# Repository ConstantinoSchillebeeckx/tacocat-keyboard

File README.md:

# tacocat keyboard

:construction: this repo is currently on *hold*; once I started writing the firmware, I realized the choice of microcontroller was not a good one. For a keyboard, it's super useful to have a USB to serial chip that acts like a [HID](https://en.wikipedia.org/wiki/Human_interface_device), that's why the Teensy or the ATmega32U4 are popular options. That being said, I started developing the firmware in such a way that required a python script to be running on the host to listen to the keystrokes being sent. :sweat: Furthermore, I'm not convinced that the physical layout is that great. Anywho, I'm leaving this here for reference. :construction:

<br>
<br>

Another split ergonomic keyboard with features:
- two symmetric keyboard halves staggered in opposite directions
- wireless or powered operation
- wifi & bluetooth connected
- can be used as two halves with a TRRS audio cable or as single joined keyboard (no cable needed)
- audio passthrough

Please visit the [wiki](https://github.com/ConstantinoSchillebeeckx/tacocat-keyboard/wiki) for full documentation and build logs.

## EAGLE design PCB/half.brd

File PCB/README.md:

# PCB

The PCB was designed to be symmetric so that the same half could be used for both the left and the right side of the keyboard; the PCB simply needs to be flipped over depending on the side that is used.

Features:
- two symmetric keyboard halves
- wireless or powered operation
- wifi & bluetooth connected
- can be used as two halves with a TRRS audio cable or as single joined keyboard (no cable needed)
- audio passthrough

The board can be ordered from OshPark by clicking the image below.

<a href="https://oshpark.com/shared_projects/jsQ9hCTr"></img></a>

## Notes

To populate, place all Cherry MX switches, LEDs, diodes, capacitors and resistors on the *top* side of the board; the ESP32 and all IO jacks are placed on the *bottom* of the PCB.

Also:
- the top TRRS jack may hit one of the alignment pins of the switch; this pins may have to be manually cut
- the male I2C connection has plastic alignment pins that will only fit into the PCB after the two existing holes (used by the female end) are drilled out to a diamter of 1mm

## BOM

The items listed below are for two keyboard halves; an [online BOM](https://www.digikey.com/classic/RegisteredUser/BOMBillOfMaterials.aspx?path=1&exist=1&id=5155922) has also been generated for ease of purchase.

**NOTE:** the BOM listed includes various USB & TRRS jacks needed to build custom cables for the project, however the list does not include the wires needed to build the cables. You'll need to source a 5 conductor cable to connect the keyboard halves and an 8 conductor cable (4 for USB, 4 for TRRS) for the cable connecting the keyboard to the computer.

## Layout

#### Circuit schematic

#### PCB top

#### PCB bottom

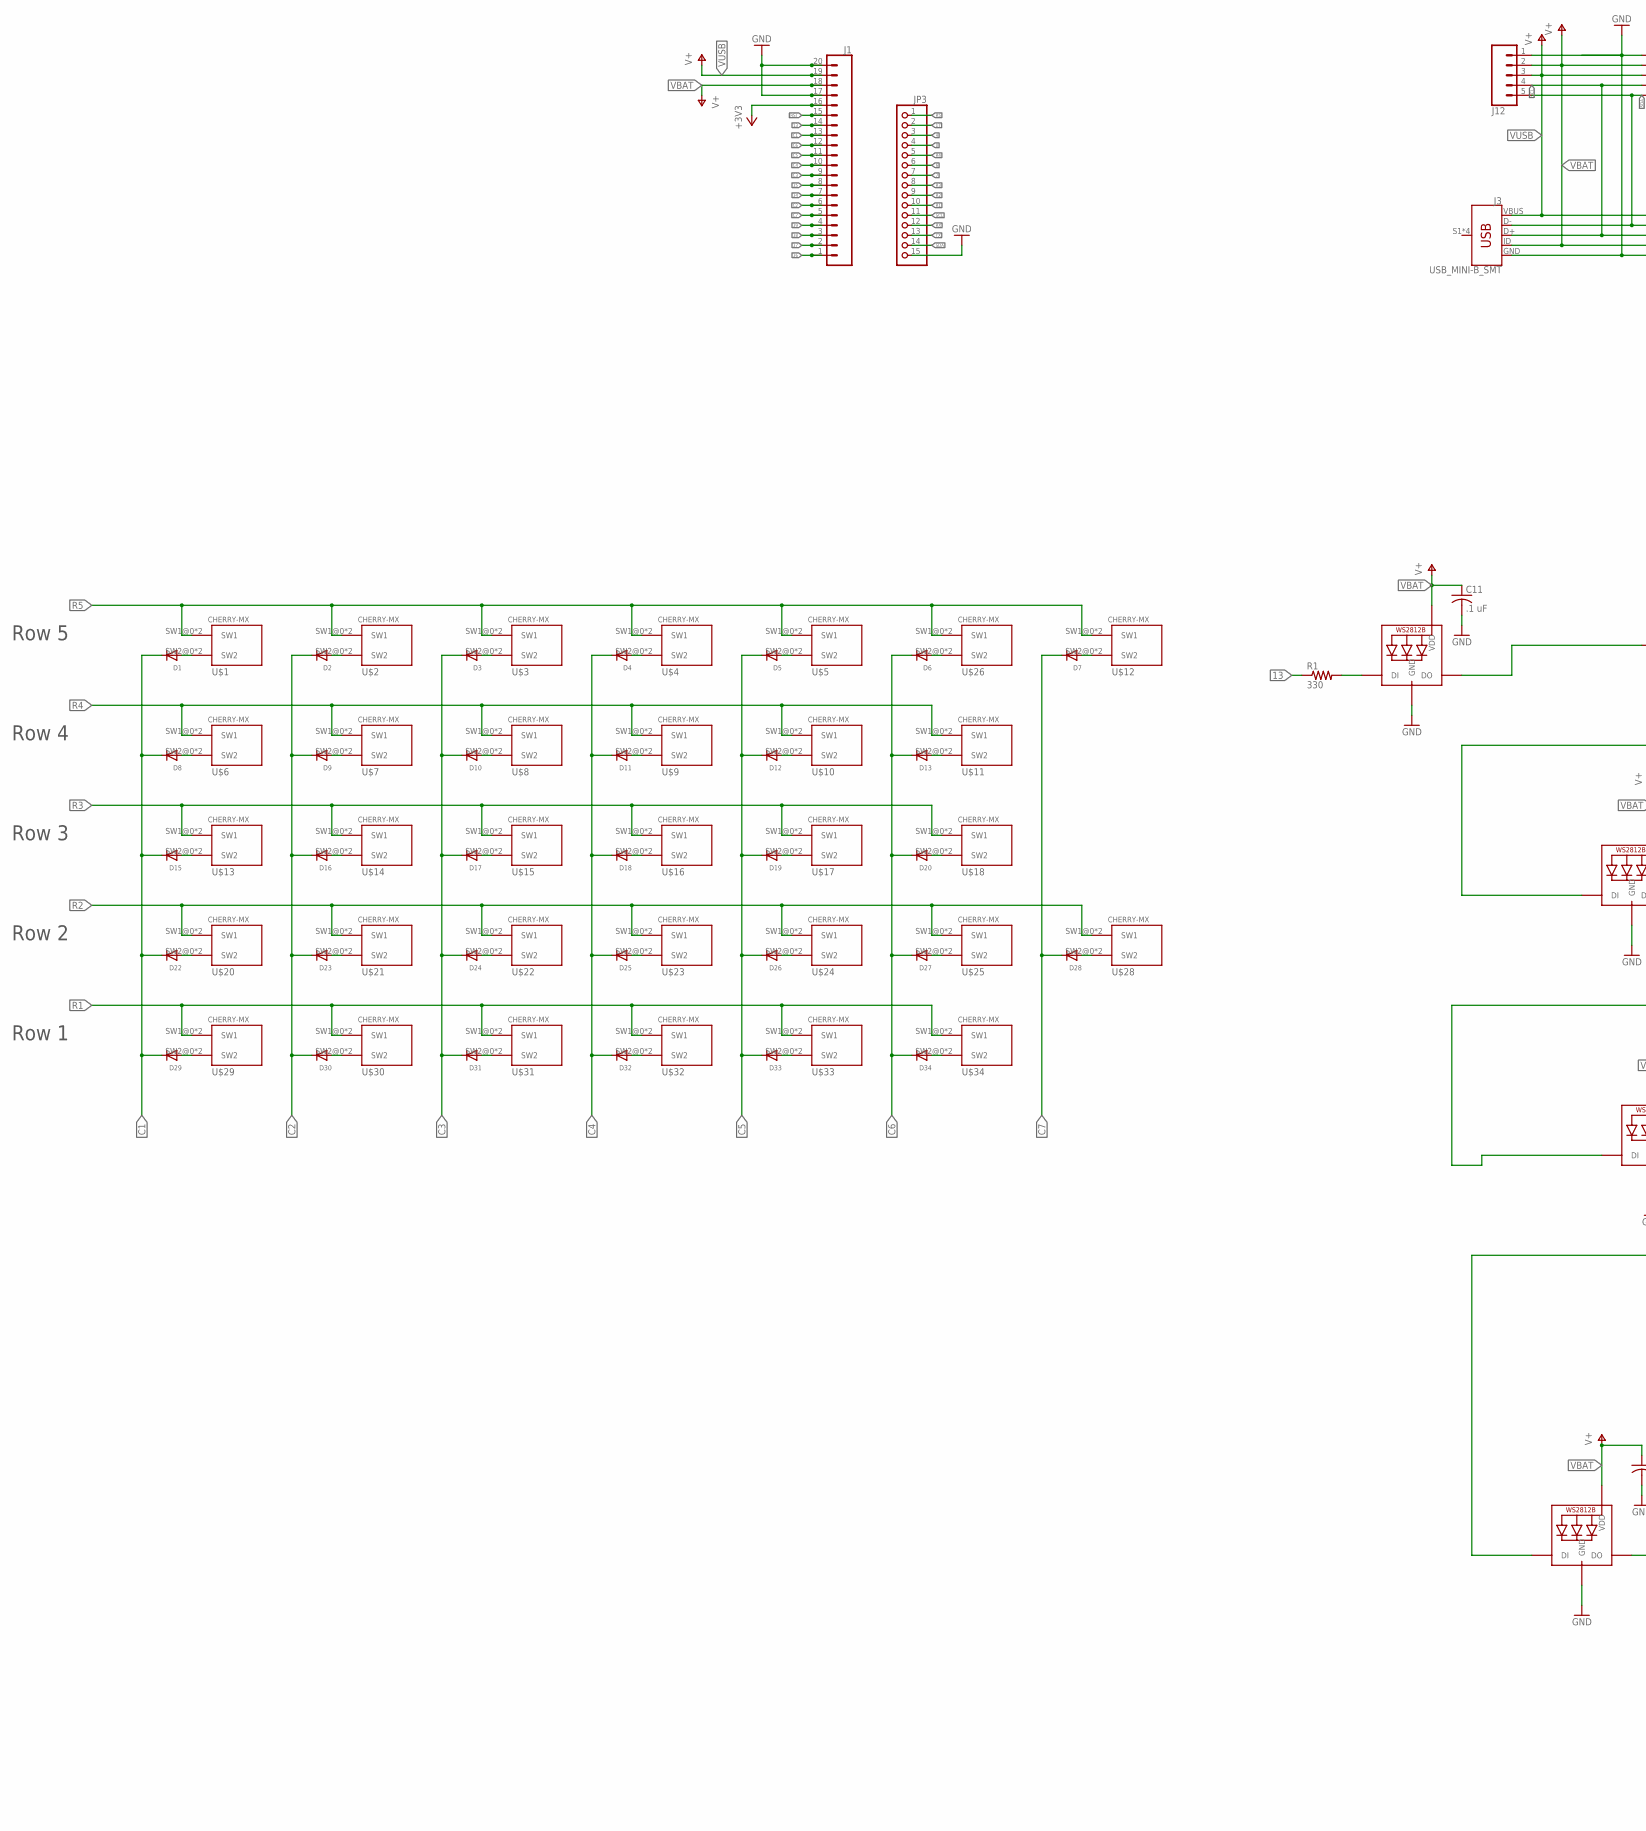
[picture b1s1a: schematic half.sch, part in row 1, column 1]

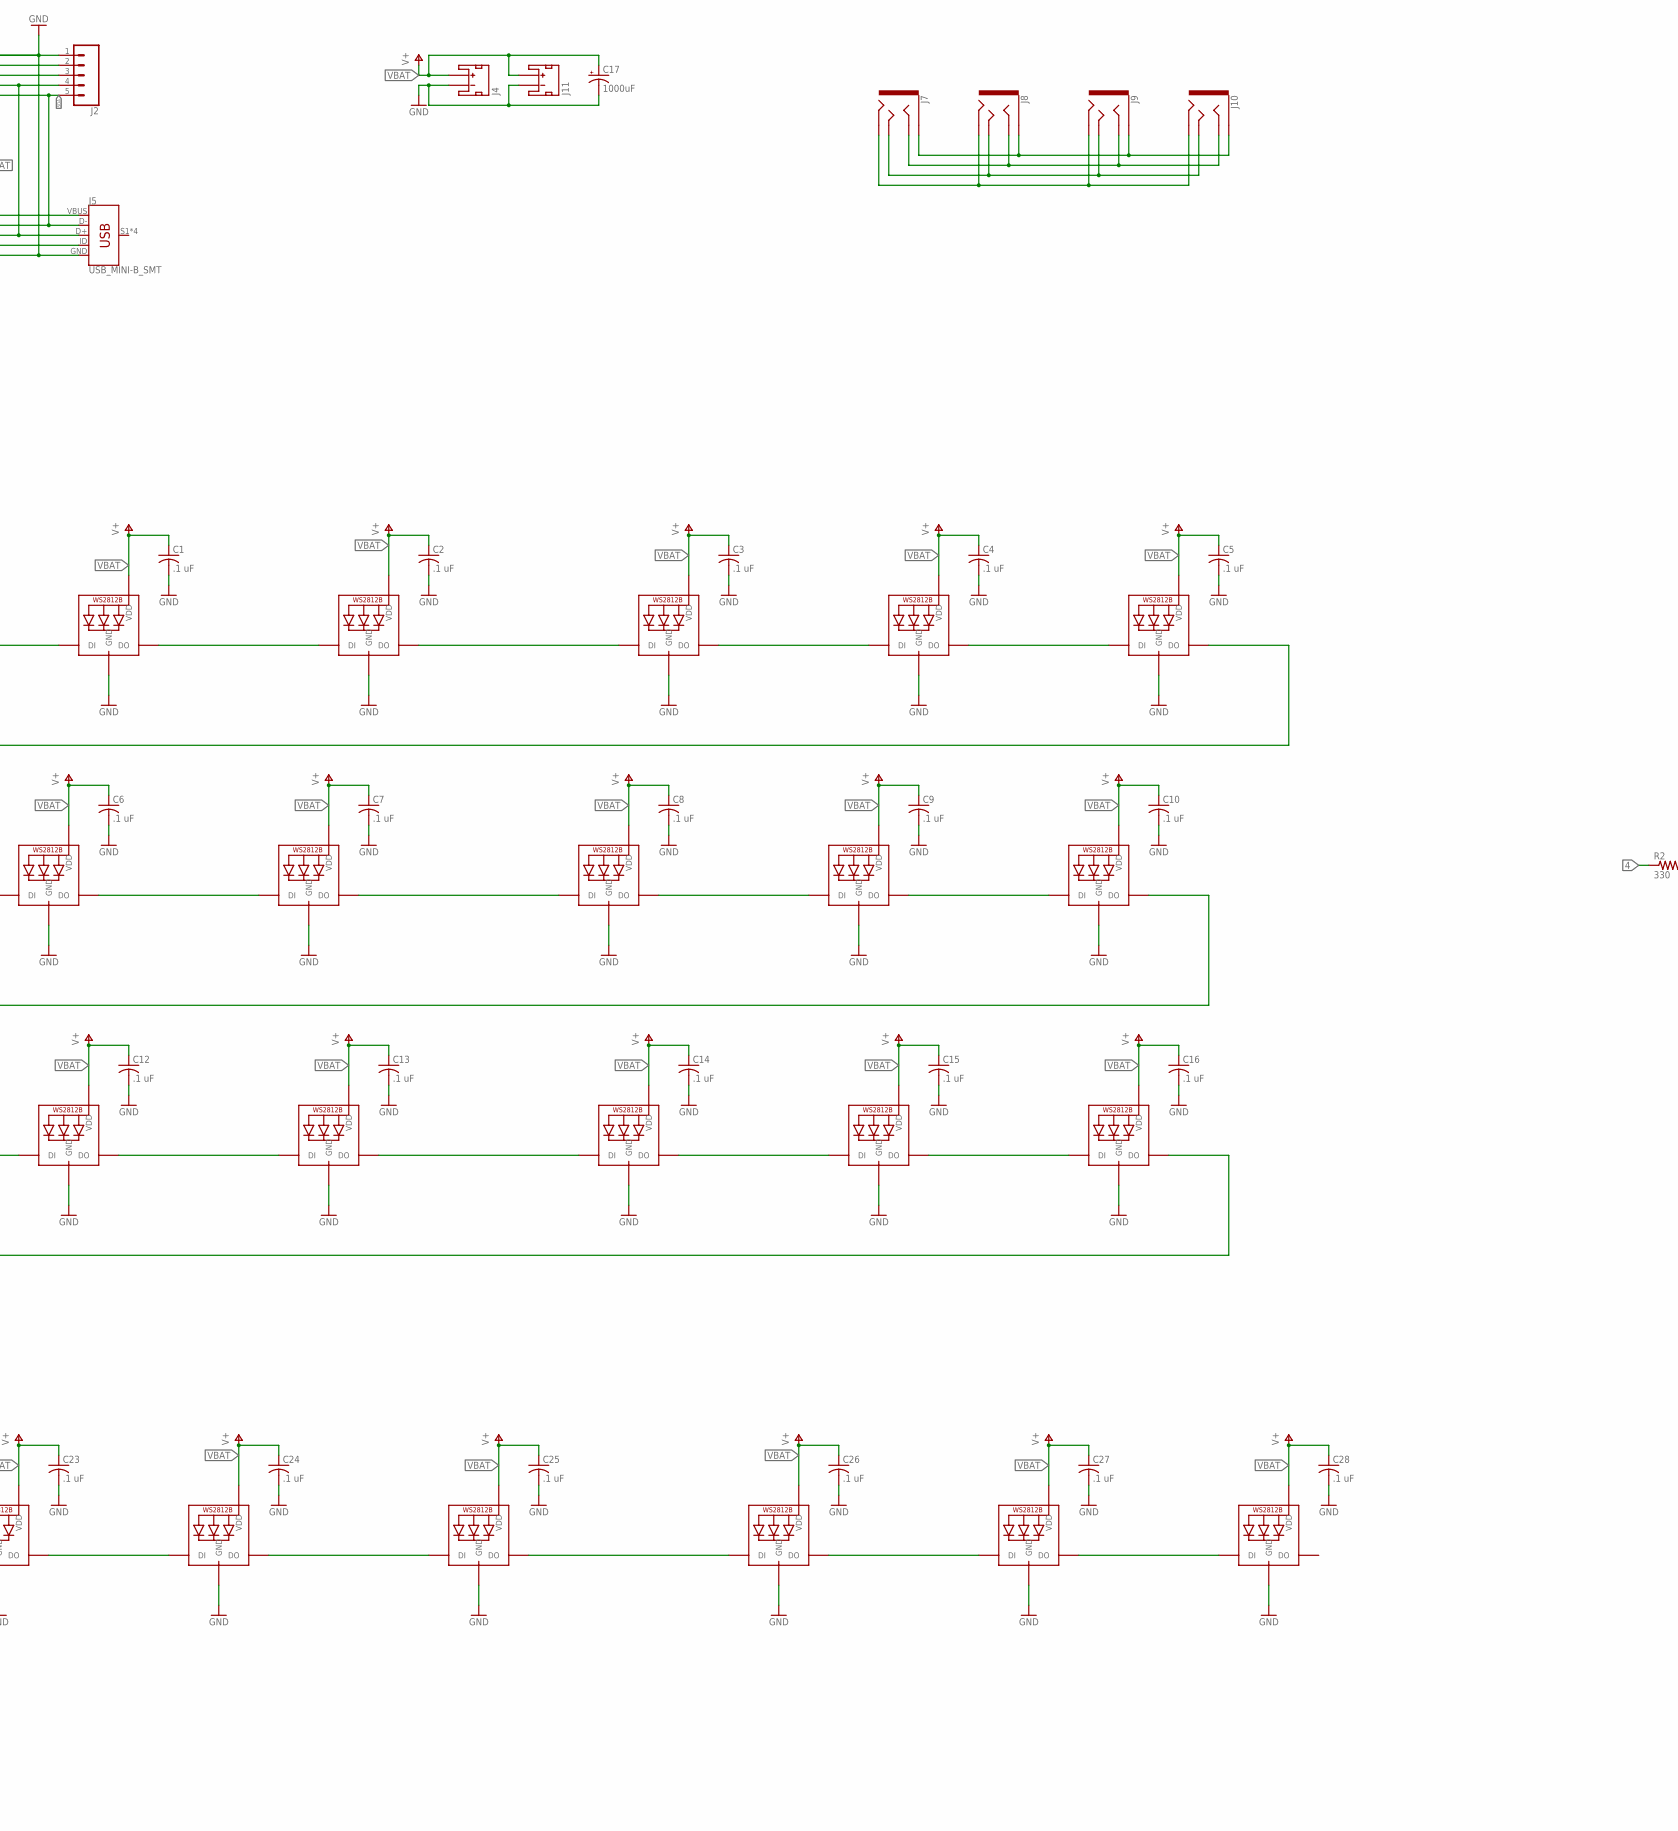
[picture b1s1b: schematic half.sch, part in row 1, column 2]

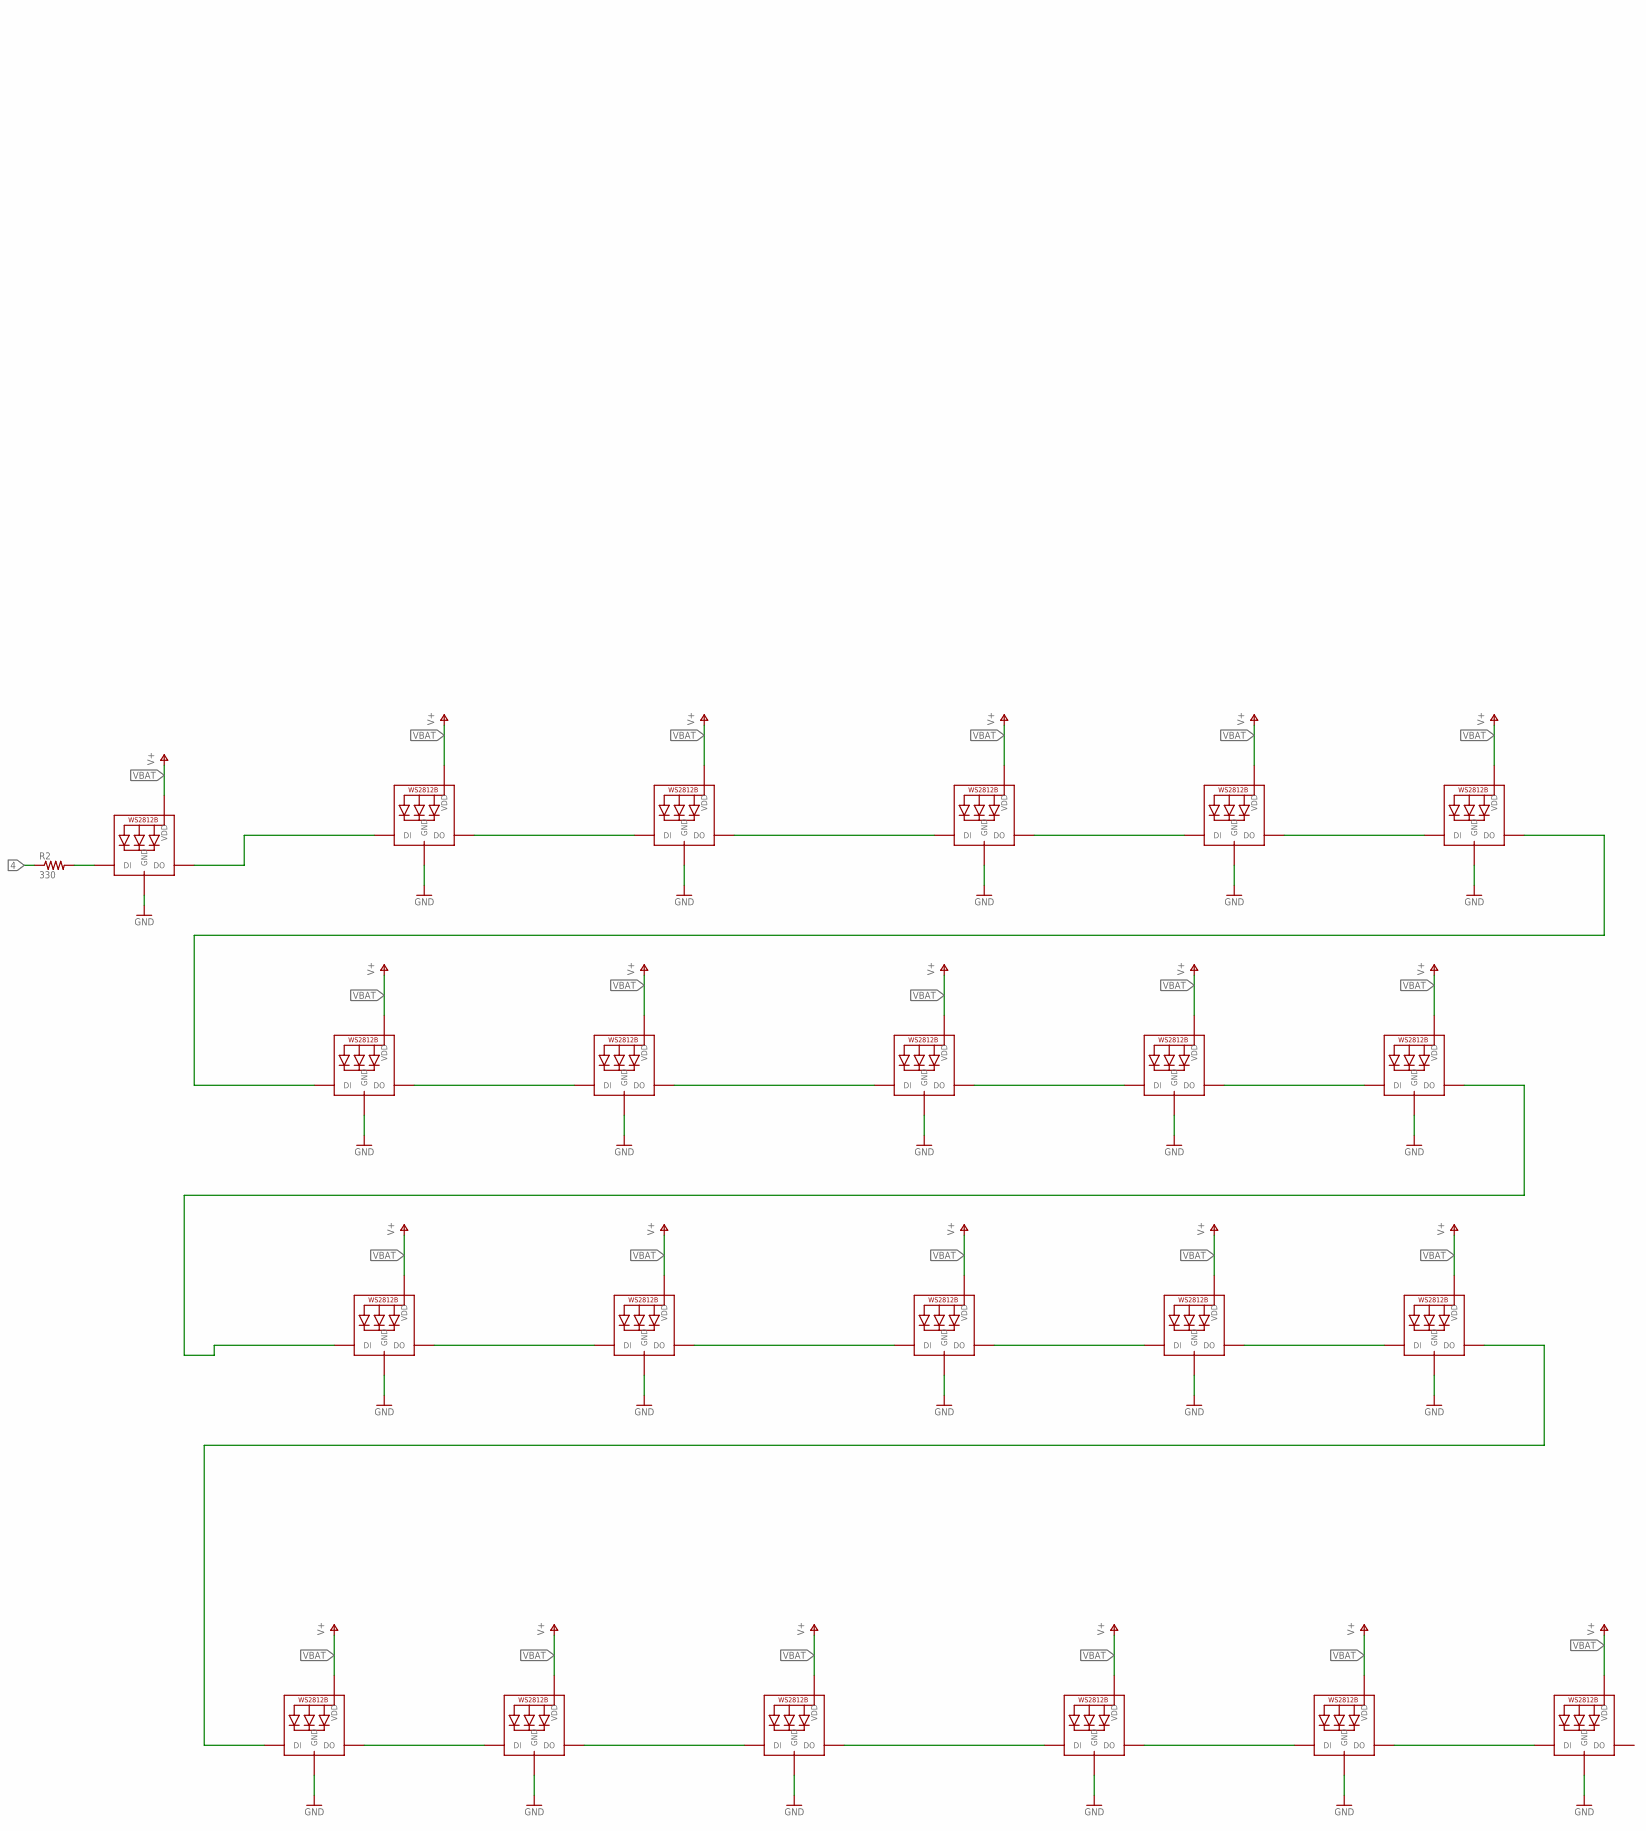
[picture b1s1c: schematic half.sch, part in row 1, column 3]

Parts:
C1, C2, C3, C4, C5, C6, C7, C8, C9, C10, C11, C12, C13, C14, C15, C16, C23, C24, C25, C26, C27, C28: .1 uF; C025-025X050
C17: 1000uF; E3,5-8
D1, D2, D3, D4, D5, D6, D7, D8, D9, D10, D11, D12, D13, D15, D16, D17, D18, D19, D20, D22, D23, D24, D25, D26, D27, D28, D29, D30, D31, D32, D33, D34: DIODEDO-1N4148; DO-1N4148
J1: CONN_20NOSILK; 1X20_NOSILK
J2: CONN_05NO_SILK_SMALL; 1X05_NO_SILK_SMALL
J3, J5: USB_MINI-B_SMT; USB-MINIB
J4, J11: JST_2MM_MALE; JST-2-SMD
J7, J8, J9, J10: AUDIO_JACK_TRRSSMD_RA; AUDIO_JACK_3.5MM_TRRS_SMD_RA
J12: CONN_05NO_SILK; 1X05_NO_SILK
JP3: PINHD-1X15-CB; 1X15-CB
LED1, LED2, LED3, LED4, LED5, LED6, LED7, LED8, LED9, LED10, LED11, LED12, LED13, LED14, LED15, LED16, LED17, LED18, LED19, LED20, LED21, LED22, LED23, LED24, LED25, LED26, LED27, LED28, LED29, LED30, LED31, LED32, LED33, LED34, LED35, LED36, LED37, LED38, LED39, LED40, LED41, LED42, LED43, LED44: WS2812BLONGPADS; WS2812B-NARROW-PADS
R1, R2: 330; 0204/7
U$1, U$2, U$3, U$4, U$5, U$6, U$7, U$8, U$9, U$10, U$11, U$12, U$13, U$14, U$15, U$16, U$17, U$18, U$20, U$21, U$22, U$23, U$24, U$25, U$26, U$28, U$29, U$30, U$31, U$32, U$33, U$34: CHERRY-MXSYMM-NOSILK; CHERRY-MX-SYMM-NOSILK

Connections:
0: JP3.4
4: JP3.3, R2.1
6: JP3.6
7: JP3.7
13: J1.14, R1.1
17: JP3.2
34: J1.7
35: J1.8
36: J1.1
37: J1.2
38: J1.3
39: J1.4
+3V3: J1.16
C1: D1.C, D8.C, D15.C, D22.C, D29.C, J1.13
C2: D2.C, D9.C, D16.C, D23.C, D30.C, J1.6
C3: D3.C, D10.C, D17.C, D24.C, D31.C, J1.9
C4: D4.C, D11.C, D18.C, D25.C, D32.C, J1.10
C5: D5.C, D12.C, D19.C, D26.C, D33.C, J1.11
C6: D6.C, D13.C, D20.C, D27.C, D34.C, J1.12
C7: D7.C, D28.C, J1.5
GND: C1.2, C2.2, C3.2, C4.2, C5.2, C6.2, C7.2, C8.2, C9.2, C10.2, C11.2, C12.2, C13.2, C14.2, C15.2, C16.2, C17.-, C23.2, C24.2, C25.2, C26.2, C27.2, C28.2, J1.17, J1.20, J2.1, J3.GND, J4.1 (-), J5.GND, J11.1 (-), J12.1, JP3.15, LED1.3-GND (GND), LED2.3-GND (GND), LED3.3-GND (GND), LED4.3-GND (GND), LED5.3-GND (GND), LED6.3-GND (GND), LED7.3-GND (GND), LED8.3-GND (GND), LED9.3-GND (GND), LED10.3-GND (GND), LED11.3-GND (GND), LED12.3-GND (GND), LED13.3-GND (GND), LED14.3-GND (GND), LED15.3-GND (GND), LED16.3-GND (GND), LED17.3-GND (GND), LED18.3-GND (GND), LED19.3-GND (GND), LED20.3-GND (GND), LED21.3-GND (GND), LED22.3-GND (GND), LED23.3-GND (GND), LED24.3-GND (GND), LED25.3-GND (GND), LED26.3-GND (GND), LED27.3-GND (GND), LED28.3-GND (GND), LED29.3-GND (GND), LED30.3-GND (GND), LED31.3-GND (GND), LED32.3-GND (GND), LED33.3-GND (GND), LED34.3-GND (GND), LED35.3-GND (GND), LED36.3-GND (GND), LED37.3-GND (GND), LED38.3-GND (GND), LED39.3-GND (GND), LED40.3-GND (GND), LED41.3-GND (GND), LED42.3-GND (GND), LED43.3-GND (GND), LED44.3-GND (GND)
unnamed: D1.A, U$1.SW2@0 (SW2), U$1.SW2@1 (SW2)
unnamed: D28.A, U$28.SW2@0 (SW2), U$28.SW2@1 (SW2)
unnamed: D8.A, U$6.SW2@0 (SW2), U$6.SW2@1 (SW2)
unnamed: D15.A, U$13.SW2@0 (SW2), U$13.SW2@1 (SW2)
unnamed: D22.A, U$20.SW2@0 (SW2), U$20.SW2@1 (SW2)
unnamed: D29.A, U$29.SW2@0 (SW2), U$29.SW2@1 (SW2)
unnamed: D7.A, U$12.SW2@0 (SW2), U$12.SW2@1 (SW2)
unnamed: D2.A, U$2.SW2@0 (SW2), U$2.SW2@1 (SW2)
unnamed: D9.A, U$7.SW2@0 (SW2), U$7.SW2@1 (SW2)
unnamed: D16.A, U$14.SW2@0 (SW2), U$14.SW2@1 (SW2)
unnamed: D30.A, U$30.SW2@0 (SW2), U$30.SW2@1 (SW2)
unnamed: D31.A, U$31.SW2@0 (SW2), U$31.SW2@1 (SW2)
unnamed: D24.A, U$22.SW2@0 (SW2), U$22.SW2@1 (SW2)
unnamed: D17.A, U$15.SW2@0 (SW2), U$15.SW2@1 (SW2)
unnamed: D10.A, U$8.SW2@0 (SW2), U$8.SW2@1 (SW2)
unnamed: D3.A, U$3.SW2@0 (SW2), U$3.SW2@1 (SW2)
unnamed: D4.A, U$4.SW2@0 (SW2), U$4.SW2@1 (SW2)
unnamed: D11.A, U$9.SW2@0 (SW2), U$9.SW2@1 (SW2)
unnamed: D18.A, U$16.SW2@0 (SW2), U$16.SW2@1 (SW2)
unnamed: D25.A, U$23.SW2@0 (SW2), U$23.SW2@1 (SW2)
unnamed: D32.A, U$32.SW2@0 (SW2), U$32.SW2@1 (SW2)
unnamed: D33.A, U$33.SW2@0 (SW2), U$33.SW2@1 (SW2)
unnamed: D26.A, U$24.SW2@0 (SW2), U$24.SW2@1 (SW2)
unnamed: D19.A, U$17.SW2@0 (SW2), U$17.SW2@1 (SW2)
unnamed: D12.A, U$10.SW2@0 (SW2), U$10.SW2@1 (SW2)
unnamed: D5.A, U$5.SW2@0 (SW2), U$5.SW2@1 (SW2)
unnamed: D6.A, U$26.SW2@0 (SW2), U$26.SW2@1 (SW2)
unnamed: D13.A, U$11.SW2@0 (SW2), U$11.SW2@1 (SW2)
unnamed: D20.A, U$18.SW2@0 (SW2), U$18.SW2@1 (SW2)
unnamed: D27.A, U$25.SW2@0 (SW2), U$25.SW2@1 (SW2)
unnamed: D34.A, U$34.SW2@0 (SW2), U$34.SW2@1 (SW2)
unnamed: LED1.2-DOUT (DO), LED18.4-DIN (DI)
unnamed: LED18.2-DOUT (DO), LED19.4-DIN (DI)
unnamed: LED19.2-DOUT (DO), LED20.4-DIN (DI)
unnamed: J7.RING1, J8.RING1, J9.RING1, J10.RING1
unnamed: LED13.4-DIN (DI), LED22.2-DOUT (DO)
unnamed: D23.A, U$21.SW2@0 (SW2), U$21.SW2@1 (SW2)
unnamed: LED20.2-DOUT (DO), LED21.4-DIN (DI)
unnamed: LED13.2-DOUT (DO), LED14.4-DIN (DI)
unnamed: LED14.2-DOUT (DO), LED15.4-DIN (DI)
unnamed: LED21.2-DOUT (DO), LED22.4-DIN (DI)
unnamed: J7.TIP, J8.TIP, J9.TIP, J10.TIP
unnamed: J7.RING2, J8.RING2, J9.RING2, J10.RING2
unnamed: J7.EARTH, J8.EARTH, J9.EARTH, J10.EARTH
unnamed: LED30.4-DIN (DI), LED39.2-DOUT (DO)
unnamed: LED24.4-DIN (DI), LED34.2-DOUT (DO)
unnamed: LED1.4-DIN (DI), R1.2
unnamed: LED15.2-DOUT (DO), LED16.4-DIN (DI)
unnamed: LED8.2-DOUT (DO), LED9.4-DIN (DI)
unnamed: LED9.2-DOUT (DO), LED10.4-DIN (DI)
unnamed: LED10.2-DOUT (DO), LED11.4-DIN (DI)
unnamed: LED2.2-DOUT (DO), LED3.4-DIN (DI)
unnamed: LED8.4-DIN (DI), LED17.2-DOUT (DO)
unnamed: LED3.2-DOUT (DO), LED4.4-DIN (DI)
unnamed: LED4.2-DOUT (DO), LED5.4-DIN (DI)
unnamed: LED5.2-DOUT (DO), LED6.4-DIN (DI)
unnamed: LED2.4-DIN (DI), LED12.2-DOUT (DO)
unnamed: LED6.2-DOUT (DO), LED7.4-DIN (DI)
unnamed: LED11.2-DOUT (DO), LED12.4-DIN (DI)
unnamed: LED16.2-DOUT (DO), LED17.4-DIN (DI)
unnamed: LED23.4-DIN (DI), R2.2
unnamed: LED24.2-DOUT (DO), LED25.4-DIN (DI)
unnamed: LED25.2-DOUT (DO), LED26.4-DIN (DI)
unnamed: LED26.2-DOUT (DO), LED27.4-DIN (DI)
unnamed: LED27.2-DOUT (DO), LED28.4-DIN (DI)
unnamed: LED28.2-DOUT (DO), LED29.4-DIN (DI)
unnamed: LED30.2-DOUT (DO), LED31.4-DIN (DI)
unnamed: LED31.2-DOUT (DO), LED32.4-DIN (DI)
unnamed: LED32.2-DOUT (DO), LED33.4-DIN (DI)
unnamed: LED33.2-DOUT (DO), LED34.4-DIN (DI)
unnamed: LED35.4-DIN (DI), LED44.2-DOUT (DO)
unnamed: LED35.2-DOUT (DO), LED36.4-DIN (DI)
unnamed: LED36.2-DOUT (DO), LED37.4-DIN (DI)
unnamed: LED37.2-DOUT (DO), LED38.4-DIN (DI)
unnamed: LED38.2-DOUT (DO), LED39.4-DIN (DI)
unnamed: LED23.2-DOUT (DO), LED40.4-DIN (DI)
unnamed: LED40.2-DOUT (DO), LED41.4-DIN (DI)
unnamed: LED41.2-DOUT (DO), LED42.4-DIN (DI)
unnamed: LED42.2-DOUT (DO), LED43.4-DIN (DI)
unnamed: LED43.2-DOUT (DO), LED44.4-DIN (DI)
R1: JP3.10, U$29.SW1@0 (SW1), U$29.SW1@1 (SW1), U$30.SW1@0 (SW1), U$30.SW1@1 (SW1), U$31.SW1@0 (SW1), U$31.SW1@1 (SW1), U$32.SW1@0 (SW1), U$32.SW1@1 (SW1), U$33.SW1@0 (SW1), U$33.SW1@1 (SW1), U$34.SW1@0 (SW1), U$34.SW1@1 (SW1)
R2: JP3.9, U$20.SW1@0 (SW1), U$20.SW1@1 (SW1), U$21.SW1@0 (SW1), U$21.SW1@1 (SW1), U$22.SW1@0 (SW1), U$22.SW1@1 (SW1), U$23.SW1@0 (SW1), U$23.SW1@1 (SW1), U$24.SW1@0 (SW1), U$24.SW1@1 (SW1), U$25.SW1@0 (SW1), U$25.SW1@1 (SW1), U$28.SW1@0 (SW1), U$28.SW1@1 (SW1)
R3: JP3.8, U$13.SW1@0 (SW1), U$13.SW1@1 (SW1), U$14.SW1@0 (SW1), U$14.SW1@1 (SW1), U$15.SW1@0 (SW1), U$15.SW1@1 (SW1), U$16.SW1@0 (SW1), U$16.SW1@1 (SW1), U$17.SW1@0 (SW1), U$17.SW1@1 (SW1), U$18.SW1@0 (SW1), U$18.SW1@1 (SW1)
R4: JP3.5, U$6.SW1@0 (SW1), U$6.SW1@1 (SW1), U$7.SW1@0 (SW1), U$7.SW1@1 (SW1), U$8.SW1@0 (SW1), U$8.SW1@1 (SW1), U$9.SW1@0 (SW1), U$9.SW1@1 (SW1), U$10.SW1@0 (SW1), U$10.SW1@1 (SW1), U$11.SW1@0 (SW1), U$11.SW1@1 (SW1)
R5: JP3.1, U$1.SW1@0 (SW1), U$1.SW1@1 (SW1), U$2.SW1@0 (SW1), U$2.SW1@1 (SW1), U$3.SW1@0 (SW1), U$3.SW1@1 (SW1), U$4.SW1@0 (SW1), U$4.SW1@1 (SW1), U$5.SW1@0 (SW1), U$5.SW1@1 (SW1), U$12.SW1@0 (SW1), U$12.SW1@1 (SW1), U$26.SW1@0 (SW1), U$26.SW1@1 (SW1)
RST: J1.15
RX: JP3.12
SCL: J2.4, J3.D+, J5.D+, J12.4, JP3.11
SDA: J2.5, J3.D-, J5.D-, J12.5, JP3.14
TX: JP3.13
VBAT: C1.1, C2.1, C3.1, C4.1, C5.1, C6.1, C7.1, C8.1, C9.1, C10.1, C11.1, C12.1, C13.1, C14.1, C15.1, C16.1, C17.+, C23.1, C24.1, C25.1, C26.1, C27.1, C28.1, J1.18, J2.2, J3.ID, J4.2 (+), J5.ID, J11.2 (+), J12.2, LED1.1-VDD (VDD), LED2.1-VDD (VDD), LED3.1-VDD (VDD), LED4.1-VDD (VDD), LED5.1-VDD (VDD), LED6.1-VDD (VDD), LED7.1-VDD (VDD), LED8.1-VDD (VDD), LED9.1-VDD (VDD), LED10.1-VDD (VDD), LED11.1-VDD (VDD), LED12.1-VDD (VDD), LED13.1-VDD (VDD), LED14.1-VDD (VDD), LED15.1-VDD (VDD), LED16.1-VDD (VDD), LED17.1-VDD (VDD), LED18.1-VDD (VDD), LED19.1-VDD (VDD), LED20.1-VDD (VDD), LED21.1-VDD (VDD), LED22.1-VDD (VDD), LED23.1-VDD (VDD), LED24.1-VDD (VDD), LED25.1-VDD (VDD), LED26.1-VDD (VDD), LED27.1-VDD (VDD), LED28.1-VDD (VDD), LED29.1-VDD (VDD), LED30.1-VDD (VDD), LED31.1-VDD (VDD), LED32.1-VDD (VDD), LED33.1-VDD (VDD), LED34.1-VDD (VDD), LED35.1-VDD (VDD), LED36.1-VDD (VDD), LED37.1-VDD (VDD), LED38.1-VDD (VDD), LED39.1-VDD (VDD), LED40.1-VDD (VDD), LED41.1-VDD (VDD), LED42.1-VDD (VDD), LED43.1-VDD (VDD), LED44.1-VDD (VDD)
VUSB: J1.19, J2.3, J3.VBUS, J5.VBUS, J12.3

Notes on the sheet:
Row 1
Row 2
Row 3
Row 4
Row 5

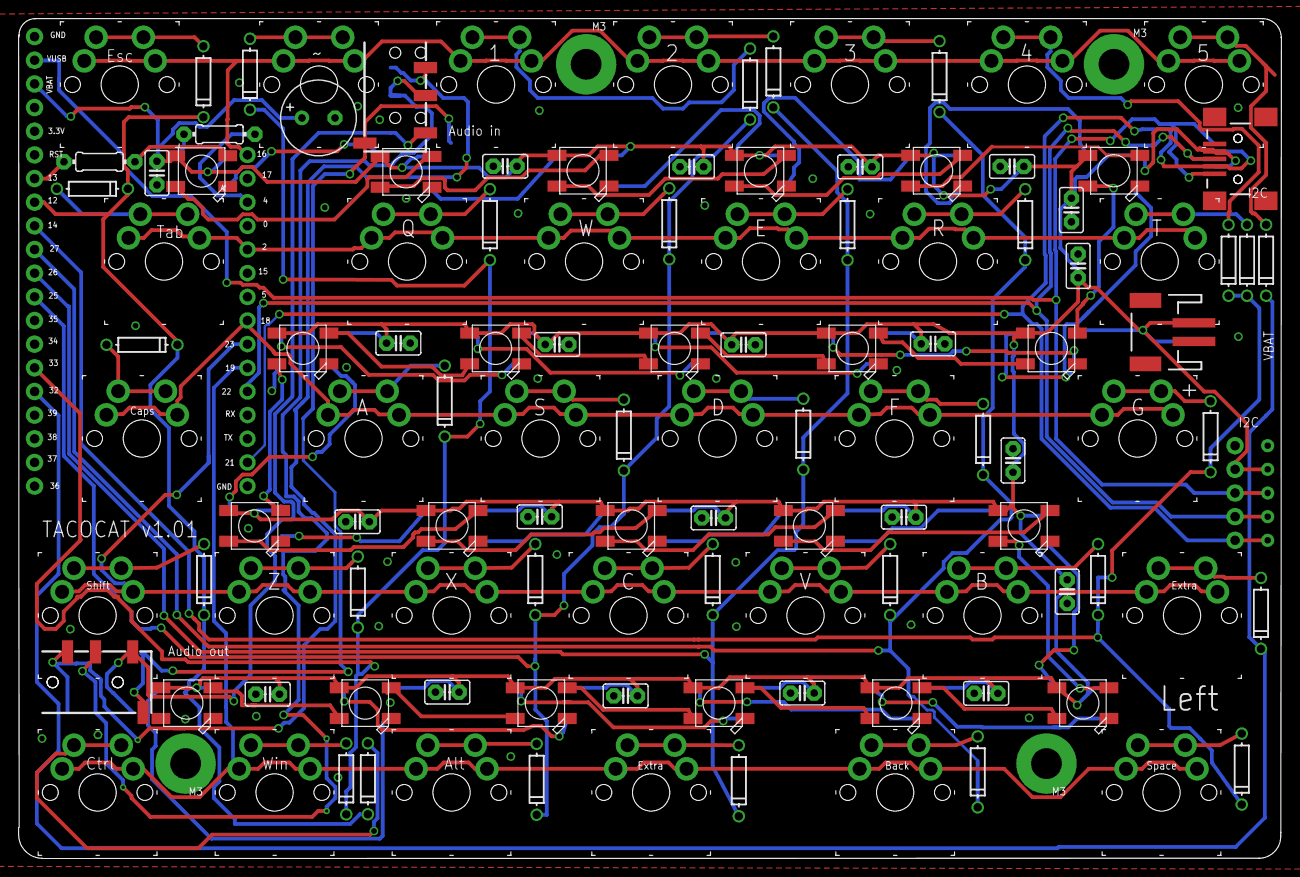
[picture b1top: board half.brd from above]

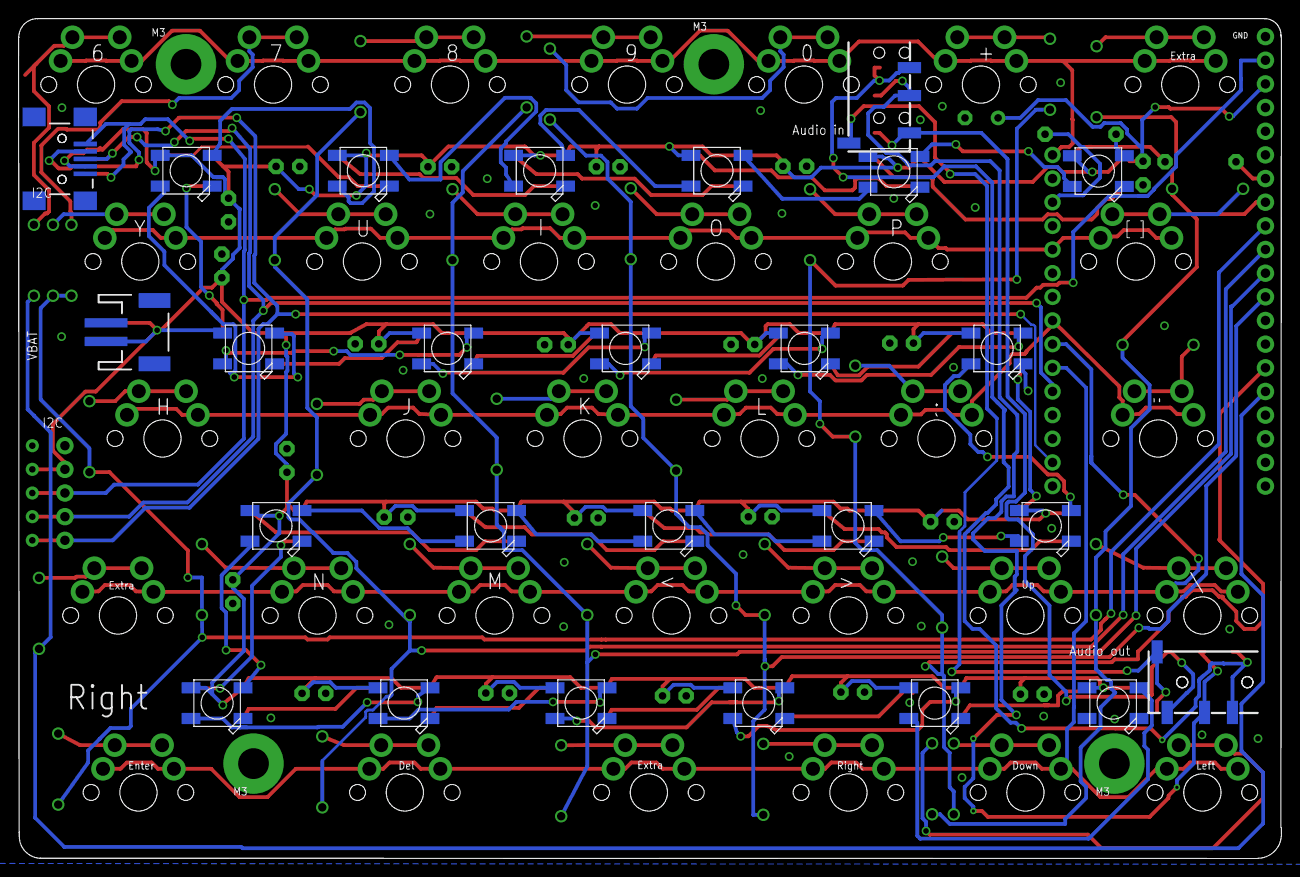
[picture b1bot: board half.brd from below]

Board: 2 copper layers, 135.6 x 90.2 mm, 145 parts (26 on the bottom side), 99 nets.

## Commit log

2017-04-03 added eagle file
2017-04-04 3d models keycaps
2017-04-04 cleanup
2017-04-04 added keycap submodule
2017-04-04 submodule switch
2017-04-04 directory rename
2017-04-04 added eagle library submodule
2017-04-11 updated PCB
2017-04-12 pcb update
2017-04-12 added tacocat img
2017-04-12 v1 of pcb
2017-04-12 pcb v1
2017-04-12 added various descriptions to README
2017-04-12 rename folder structure
2017-04-16 circuit layout
2017-04-16 fix circuit layout
2017-04-16 move laser
2017-04-18 added laser dxf
2017-04-18 comment about units
2017-04-18 render left
2017-04-18 Update LICENSE
2017-04-22 added wiki images
2017-04-22 render cam
2017-04-22 cam SS
2017-04-22 added rotation arrow
2017-04-22 layout update
2017-04-23 full render
2017-04-30 pcb image add
2017-05-01 current draw img
2017-05-06 init code
2017-05-08 PCB update, improved micro usb part with longer pads, capacitor added to VBAT circuit
2017-05-09 img keyboard layout
2017-05-09 added letter layout
2017-05-09 letter layout img type update
2017-05-09 letter alignment fix
2017-05-21 added images
2017-05-21 remove lightroom library and images
2017-05-21 add raw images, ignore library
2017-05-21 added readme for the various subdirectories
2017-08-15 code add
2017-08-21 test esp32 code
2017-09-18 i2c work
2017-12-29 update ...

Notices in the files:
parts and their libraries:
SparkFun-Connectors: Licensing: Creative Commons ShareAlike 4.0 International - https://creativecommons.org/licenses/by-sa/4.0
